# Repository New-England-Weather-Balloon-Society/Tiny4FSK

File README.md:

# Tiny4FSK - The Lightweight Horus Binary Tracker Built for HABs
**WORK IN PROGRESS** - Please do not rely on this as your only tracking system. Tiny4FSK is still in the R&D phase of development and testing.

**NEW** - Horus Binary v3! + quick lock mode and recovery mode

**STATE** - Main branch is stable!

## What is the Tiny4FSK project?
Tiny4FSK aims to be an ultra-tiny high-altitude tracking system. It runs on 1 AA battery that lasts for 10-17 hours (packet interval and power output can be adjusted to lengthen battery life). It runs on 4FSK (4-frequency shift keying), which means that it separates tones into 4 separate frequencies. Upon this, it uses the [Horus Binary v3](https://github.com/projecthorus/horusdemodlib) system, which is a relatively modern system popularly used with [RS41ng](https://github.com/mikaelnousiainen/RS41ng).

## What are High-Altitude Balloons?
High altitude balloons (HABs) allow space science enthusiasts to launch their own payloads to near-space (30km) at a cost of hundreds of dollars instead of millions of dollars.  This can be done for atmospheric research, breathtaking imagery, and scientific experimentation. While demanding meticulous planning, safety adherence, and technical skill in electronics and mechanics, this hobby rewards makers with a chance to get hands on with projects like electronic data loggers, camera systems, wireless communications, and more.
## Parts and Materials
This codebase is meant to work with the Tiny4FSK PCB, also available on this GitHub repository. Key components include:

 - **Microcontroller** - [SAMD21G18A](https://www.microchip.com/en-us/product/atsamd21g18). A modern Cortex-M0+ microcontroller by Microchip.
 - **TX Module** - [Si4063](https://www.silabs.com/wireless/proprietary/ezradiopro-sub-ghz-ics/device.si4063?tab=specs). A transceiver from Silicon Labs, similar to the Si4032 on RS41 radiosondes.
 - **GPS RX Module** - [ATGM336H](https://jlcpcb.com/partdetail/Zhongkewei-ATGM336H5N31/C90770). A cheap, high-performance GPS module from ZHONGKEWEI.
 - **Environmental Sensor** - [BME280](https://www.bosch-sensortec.com/products/environmental-sensors/humidity-sensors-bme280/). A proven sensor from Bosch for measuring temperature, pressure, and humidity.
 - **Boost Converter** - [TPS61200](https://www.ti.com/product/TPS61200). Boosts 1.5V battery level to 3.3V for the rest of the board from Texas Instruments.
 - **LDO Step-Down** - [MCP1700](https://www.microchip.com/en-us/product/mcp1700). A step-down converter from Microchip.

This list is not exhaustive. Additional components and passives are detailed in the schematic files.
## The Codebase
This code is modular and separated into several different files for easy expansion. These files are listed below:

 - **Tiny4FSK.ino** - Main Arduino file with control flow.
 - **config.h** - Configuration file for user parameters.
 - **crc_calc.cpp and crc_calc.h** - CRC16 generator files for parity bits.
 - **horus_l2.cpp and horus_l2.h** - Horus layer 2 file, Golay error correction algorithm.
 - **horus_binary_v3.cpp and horus_binary_v3.h** - Horus Binary v3 packet assembly and encoding functions.
 - **voltage.cpp and voltage.h** - Voltage detection using ADC values.
 - **si4063.cpp and si4063.h** - Si4063 driver files for radio transmission.
 - **4fsk_mod.cpp and 4fsk_mod.h** - 4FSK modulation functions.
 - **utils.cpp and utils.h** - A collection of utility functions.

# Step by Step Setup Guide
## Setting up the PCB

For pre-flight configuration, the USB board does not need to be broken off, and code can be uploaded normally by just plugging in the USB as it arrives. However, the breakout may be removed to save space during flights!

1. **Carefully** snap off the USB breakout board from the board.
2. Solder on the female 1x4 header row onto the underside of the USB breakout. Solder on the 1x4 male header row to the corresponding adjacent pins (labeled VSS, GND, D-, and D+).

3. To program the board, attach the USB breakout board as shown in the photo.  Once the board is programmed, the USB breakout board can be removed for flight.

## Antenna System
This system relies on the 70cm amateur radio band (420-450 MHz in the US), and requires an amateur radio license, issued by the FCC, to operate. A pre-cut braided copper *monopole* is included, optimized to transmit on this frequency. The included antenna is a quarter-wave monopole, meaning that the antenna is just a quarter of the wavelength of the signal, and yet it maintains a good SWR (quantification of how much signal is reflected back into the transmitter). There is a pad that supports a quarter-wave monopole, but also provides grounding pads for a coax connector if alternate antennas wish to be used.
<details>
<summary>Why does this work?</summary>
A 1/4 wave monopole antenna works by using a quarter of the wavelength of the signal, which creates a resonant frequency that efficiently radiates radio waves. The ground plane acts as a reflector, effectively doubling the antenna's length and improving signal strength and quality.
</details>
<br>

Solder the copper wire onto the center pin of the antenna connector (as depicted below).

## PCB Configuration
The Tiny4FSK PCB has many configurable operating modes, pins and power sources. This section will outline these parts of the PCB.

The PCB contains one jumper, JP1.

- **JP1** - Cut (desolder) to enable SW1 for power. During flight, the mechanical shock from the landing can cause the power switch to flip, so solder this jumper to disable this risk. (Bypasses SW1).

There are also two switches/buttons, SW1 and SW2.

- **SW1** - Battery power switch. Connects battery output to boost converter input. When the battery is connected, this functions as the main power switch.
- **SW2** - Reset button for the microcontroller.

There are two antenna pads, AE1 and AE2.
- **AE1** - L1 GPS band antenna
- **AE2** - 70cm antenna pad. For a guide to cut a proper antenna, refer to the above section.

Finally, the top left 3-row header allows for custom power options.
- **VBat** - A direct connection to the switching regulator input pin. This accepts between 1.3V and 6V.
- **GND** - Board ground.
- **3v3** - Regulated 3.3V node.

## Setting up the Code
Now that you've got all the hardware set up, time for programming!

## Setting up Arduino IDE
This project is based on the Arduino IDE workflow. Below steps outline steps necessary to install Arduino IDE and configure it for the SAMD microcontroller.

 1. Install [Arduino IDE](https://www.arduino.cc/en/software) from [here](https://www.arduino.cc/en/software).
 2. [Download the Arduino SAMD core](https://docs.arduino.cc/learn/starting-guide/cores/).
 3. Download necessary libraries from library manager:
    * Arduino Low Power (with dependencies)
    * TinyGPSPlus
    * Scheduler

**Optional** - The SAMD goes to sleep to save power. To achieve proper sleep, some edits to the SAMD core are necessary. To locate the wiring.c file on your computer, [follow this guide](https://support.arduino.cc/hc/en-us/articles/4415103213714-Find-sketches-libraries-board-cores-and-other-files-on-your-computer).

Windows: `C:/Users/[YOUR USER]/AppData/Local/Arduino15/packages/arduino/hardware/samd/1.8.14/cores/arduino`

Once there, comment out or completely delete the lines shown below:
```cpp
    // Defining VERY_LOW_POWER breaks Arduino APIs since all pins are considered INPUT at startup
    // However, it really lowers the power consumption by a factor of 20 in low power mode (0.03mA vs 0.6mA)
    #ifndef VERY_LOW_POWER
      // Setup all pins (digital and analog) in INPUT mode (default is nothing)
      for (uint32_t ul = 0 ; ul < NUM_DIGITAL_PINS ; ul++ )
      {
        pinMode( ul, INPUT ) ;
      }
    #endif
```
Arduino gives you an official warning: "This breaks Arduino APIs since all pins are considered INPUT at startup. However, it really lowers the power consumption by a factor of 20 in low power mode (0.03mA vs 0.6mA)". Testing has shown no adverse effects.

## Code Configuration
User configuration of this tracker is **required**. As this system uses amateur radio, you will need at least a Technician's level license (US). Configuration file is located in **config.h**. Open this file in Arduino IDE. Here are the parameters may need to be changed.

- `CALLSIGN` - Amateur radio callsign. This is required to stay legal!
- `CALLSIGN_WPM` - Speed to send the callsign, in morse code.
- `CALLSIGN_INTERVAL` - Interval to send the morse code callsign. Maximum interval in the US is 10 minutes.
- `FREQUENCY` - This is setting for your preferred TX frequency. The filter is optimized for 70cm radio band.
- `STATUS_LED` - Comment out to disable verbose status LEDs on PCB.
- `DEV_MODE` - Comment out for flight mode, uncomment during programming. Disables Serial and enables deep sleep modes for lower power consumption.
- `PACKET_INTERVAL` - Interval between 4FSK packets. The smaller the interval, the lower the battery life is.
- `OUTPUT_POWER` - 0-127. This is the output power of the radio module (suggested to keep at maximum).
- `FLAG_BAD_PACKET` - If the latest GPS values are bad, send out all zeroes (for time, position, speed, and altitude)(suggested).
- `QUICK_LOCK` - Quick lock mode lowers the output power and increases packet interval while the GPS doesn't have a lock. This helps with desensing the GPS receiver. Values return to previously-defined `PACKET_INTERVAL` and `OUTPUT_POWER` upon lock.
- `QUICK_LOCK_POWER` - Power level used while the GPS doesn't have a lock. Only applied if `QUICK_LOCK` mode is enabled.
- `QUICK_LOCK_INTERVAL` - Packet interval used while the GPS doesn't have a lock. Only applied if `QUICK_LOCK` mode is enabled.
- `RECOVERY_MODE` - If enabled, the tracker will send updates less frequently when on the ground to save power. Only occurs if the tracker detects it's in a flight.
- `RECOVER_MODE_INTERVAL` - Interval to transmit in recovery mode, when on the ground.
- `RECOVERY_MODE_FLIGHT_THRESHOLD` - Altitude threshold to consider ourselves in flight, in meters.
- `RECOVERY_MODE_LAND_THRESHOLD` - Altitude threshold to consider ourselves on the ground, in meters. Recovery mode will trigger below this altitude.

### Output power mapping

Approximate mapping from the `OUTPUT_POWER` numeric value to typical output in dBm:

| Value | Approx. dBm |
|------:|:-----------:|
| 127   | 19 dBm      |
| 100   | 18 dBm      |
| 80    | 16.5 dBm    |
| 60    | 14.5 dBm    |
| 40    | 11.4 dBm    |
| 20    | 5.6 dBm     |
| 0     | -45 dBm     |

<details>
<summary>How do I change these values?</summary>
If there is a pre-existing number or value next to the name of the setting name, you can replace that value with the desired value (e.g. replace the "N0CALL" with your callsign in double quotes, "W0MXX"). If there is no value next to the name, you need to comment out the setting to disable that functionality, or uncomment to enable that functionality (comments are defined by adding // at the start of the line).
</details>

<details>
<summary>A note on reprogramming without DEV_MODE, or: Why does the board continuously disconnect from the computer?</summary>
On the condition that DEV_MODE is uncommented, the microcontroller goes into deep sleep to conserve power. Part of this sleep cycle includes disabling the USB peripheral, causing the board to appear to continuously disconnect and reconnect. <em>This can easily be fixed by double-clicking the reset button. Doing so will enter the board into bootloader mode, which will attach the board onto a new USB port and disable any code. Once new code is uploaded, the board will appear on a different port on the computer.</em>
</details>

## Battery Life Expectations
Through a series of battery life tests on ground-level, we've created a graph approximating the battery life with reference to packet interval and transmit power.

These graphs only provide an approximation. Variation will still occur from battery to battery, and we always recommend testing yourself prior to flight and aiming for double the battery life necessary.

At maximum power (127):

All power levels from 0 (no amplifier) to 127 (max power):

All tests ran with quick lock off and 1x Energizer Ultimate Lithium AA.

## Upload the Code!
Once code configuration is complete, you may plug in a standard data USB-C cable into the breakout board, select the port in Arduino IDE, and select the upload button (marked by an arrow at the top). You should select the `Arduino Zero (Native USB Port)` as the board name.

## Testing
Once the code is uploaded, you'll see the green LED pulse briefly to indicate initialization. The behavior of that LED is outlined [here](#led-default-behavior). Now you'll need to set up a receive station on either a [laptop and an RTL-SDR](https://github.com/projecthorus/horusdemodlib/wiki/1.1-Horus-GUI-Reception-Guide-(Windows-Linux-OSX)), [Raspberry Pi and RTL-SDR](https://github.com/projecthorus/horusdemodlib/wiki/1.2--Raspberry-Pi-'Headless'-RX-Guide), or [any browser-enabled device with an RTL-SDR](https://horus.sondehub.org).

You should start decoding packets transmitted from the board with your configuration parameters. It may take up to 5 minutes to gain a GPS fix, depending on your location.

## LED Default Behavior

| Green LED Behavior | Meaning |
|--------------------|---------|
| Single 1s pulse    | GPS detected / Airborne mode set (single pulse during initialization) |
| Single 0.5s pulse  | Packet transmission (packet build / transmit — single short pulse) |
| Off                | Idle or deep sleep (no continuous blinking) |

## External Sensors
Tiny4FSK now offers compatibility with external sensors by automatically scanning I2C on startup. Some sensors come with the Tiny4FSK General Shield, which can be found on the [GitHub Repository](https://github.com/mpkendall/Tiny4FSK-Ecosystem). If you have any custom sensors which you would like me to add support for, please raise an [issue](https://github.com/New-England-Weather-Balloon-Society/Tiny4FSK/issues).

## PCBWay PCBs
The Revision 4 PCBs have been fabricated and assembled through PCBWay. Their high-quality fabrication and assembly services are truly commendable. I appreciated the ability to choose from many different component suppliers to select the exact components I needed. Additionally, their customer service is incredibly responsive and helpful, and quickly notified me of design issues. I highly recommend PCBWay for any of your PCB prototyping & assembly needs. Thank you, PCBWay, for graciously sponsoring this project!

## Contact Me!
To ask questions, kindly donate, or even say hi, feel free to contact me at this email: tiny4fsk@gmail.com. Thanks!

## Cited Works and Sources
- [RS41ng Project](https://github.com/mikaelnousiainen/RS41ng)
- [Horus Binary modulator and decoder repository](https://github.com/projecthorus/horusdemodlib)
- [SAMD21 product page](https://www.microchip.com/en-us/product/atsamd21g18)
- [Si4063 product page](https://www.silabs.com/wireless/proprietary/ezradiopro-sub-ghz-ics/device.si4063)
- [ATGM336H product page](https://www.u-blox.com/en/product/max-m10-series)
- [BME280 product page](https://www.bosch-sensortec.com/products/environmental-sensors/humidity-sensors-bme280)
- [TPS61200 product page](https://www.ti.com/product/TPS61200)
- [MCP1700 product page](https://www.microchip.com/en-us/product/mcp1700)

## Special Thanks
This project would not be possible without the following individuals:
 - Charlie Nicholson KC1SFR for collaboration.
 - Mark Jessop VK5QI for extensive support.
 - Mike Hojnowski KD2EAT for helping out with software and hardware issues.
 - Bob Phinney K5TEC for providing funding for this project.
 - Brett Miwa for schematic and PCB design help.
 - Joe KM1P for RF help.
 - My parents for motivation.

And these entities:
 - PCBWay for PCB prototyping and sponsorship!
 - Bagel Fund for sponsorship!
 - Hack Club for support and sponsorship!
 - New England Sci-Tech for providing a makerspace.
 - Sci-Tech Amateur Radio Society for expertise.
 - New England Weather Balloon Society for insights.
 - Digikey for part sourcing.

## License
Software and Documentation:
- [GNU GPL v3 license](https://choosealicense.com/licenses/gpl-3.0/)

Hardware License:
- [OSHW (US002611)](https://certification.oshwa.org/us002611.html) and [CERN Open Hardware Licence Version 2 - Weakly Reciprocal](https://choosealicense.com/licenses/cern-ohl-w-2.0/)

## Pictures

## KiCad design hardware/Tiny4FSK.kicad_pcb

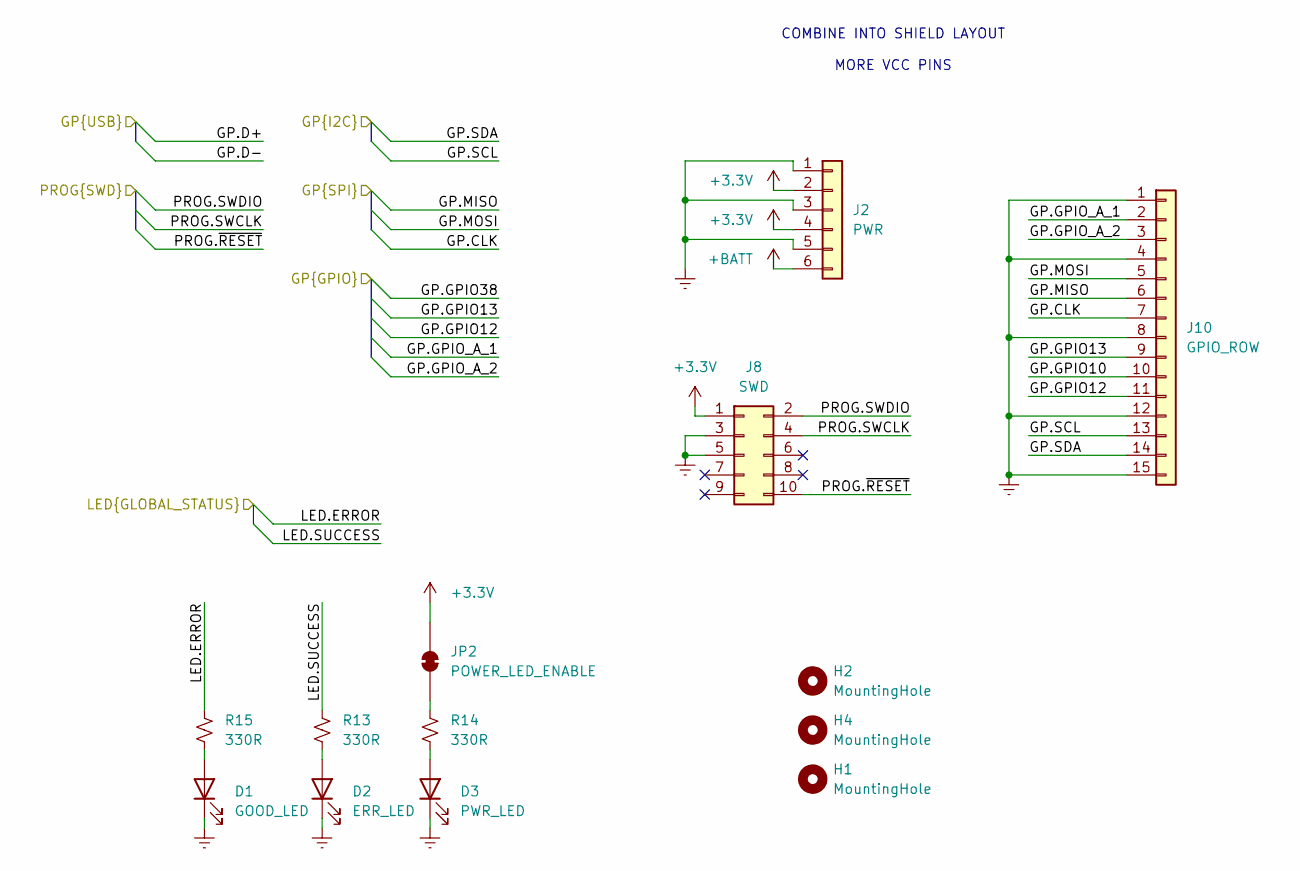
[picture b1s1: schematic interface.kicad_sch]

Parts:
D1: GOOD_LED; LED_0603_1608Metric; LCSC C2297
D2: ERR_LED; LED_0603_1608Metric; LCSC C84256
D3: PWR_LED; LED_0603_1608Metric; LCSC C84256
H1, H2, H4: MountingHole; MountingHole_2.2mm_M2
J2: PWR; PinHeader_1x06_P2.54mm_Vertical
J8: SWD; Pogo_2x05_P1.27mm
J10: GPIO_ROW; PinHeader_1x15_P2.54mm_Vertical
JP2: POWER_LED_ENABLE; SolderJumper-2_P1.3mm_Bridged_RoundedPad1.0x1.5mm
R13, R14, R15: 330R; C_0402_1005Metric; LCSC C23138

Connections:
+3.3V: J2.2, J2.4, J8.1, JP2.2 (B); also elsewhere on the board
+BATT: J2.6; also elsewhere on the board
/interface/GP.CLK: J10.7; also elsewhere on the board
/interface/GP.GPIO10: J10.10; also elsewhere on the board
/interface/GP.GPIO12: J10.11; also elsewhere on the board
/interface/GP.GPIO13: J10.9; also elsewhere on the board
/interface/GP.GPIO_A_1: J10.2; also elsewhere on the board
/interface/GP.GPIO_A_2: J10.3; also elsewhere on the board
/interface/GP.MISO: J10.6; also elsewhere on the board
/interface/GP.MOSI: J10.5; also elsewhere on the board
/interface/GP.SCL: J10.13; also elsewhere on the board
/interface/GP.SDA: J10.14; also elsewhere on the board
/interface/LED.ERROR: R15.1; also elsewhere on the board
/interface/LED.SUCCESS: R13.1; also elsewhere on the board
/interface/PROG.SWCLK: J8.4; also elsewhere on the board
/interface/PROG.SWDIO: J8.2; also elsewhere on the board
/interface/PROG.~RESET: J8.10; also elsewhere on the board
Earth: D1.1 (K), D2.1 (K), D3.1 (K), J2.1, J2.3, J2.5, J8.3, J8.5, J10.1, J10.4, J10.8, J10.12, J10.15; also elsewhere on the board
unnamed: D1.2 (A), R15.2
unnamed: D2.2 (A), R13.2
unnamed: D3.2 (A), R14.2
unnamed: JP2.1 (A), R14.1

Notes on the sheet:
COMBINE INTO SHIELD LAYOUT MORE VCC PINS

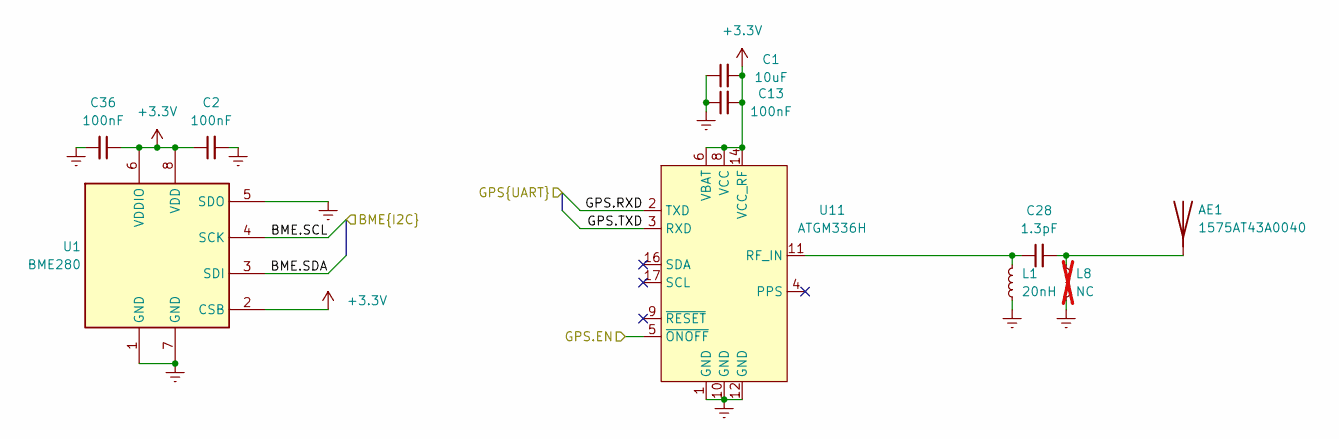
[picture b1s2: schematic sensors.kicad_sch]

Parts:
AE1: 1575AT43A0040; ANT_1575AT_JOT; LCSC C239243
C1: 10uF; C_0402_1005Metric; LCSC C19702
C2, C36: 100nF; C_0402_1005Metric; LCSC C52923
C13: 100nF; C_0402_1005Metric; LCSC C1525
C28: 1.3pF; C_0402_1005Metric; LCSC C1525
L1: 20nH; C_0402_1005Metric; LCSC C307609
L8: NC; L_0402_1005Metric; LCSC C307609; not fitted
U1: BME280; Bosch_LGA-8_2.5x2.5mm_P0.65mm_ClockwisePinNumbering; LCSC C92489
U11: ATGM336H; ublox_MAX

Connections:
+3.3V: C1.2, C2.1, C13.2, C36.1, U1.2 (CSB), U1.6 (VDDIO), U1.8 (VDD), U11.6 (VBAT), U11.8 (VCC), U11.14 (VCC_RF); also elsewhere on the board
/interface/GP.SCL: U1.4 (SCK); also elsewhere on the board
/interface/GP.SDA: U1.3 (SDI); also elsewhere on the board
/mcu/GPS.EN: U11.5 (~ONOFF); also elsewhere on the board
/mcu/RXD: U11.2 (TXD); also elsewhere on the board
/mcu/TXD: U11.3 (RXD); also elsewhere on the board
Earth: C1.1, C2.2, C13.1, C36.2, L1.1, L8.2, U1.1 (GND), U1.5 (SDO), U1.7 (GND), U11.1 (GND), U11.10 (GND), U11.12 (GND); also elsewhere on the board
unnamed: AE1.1 (A_1), C28.2, L8.1
unnamed: C28.1, L1.2, U11.11 (RF_IN)

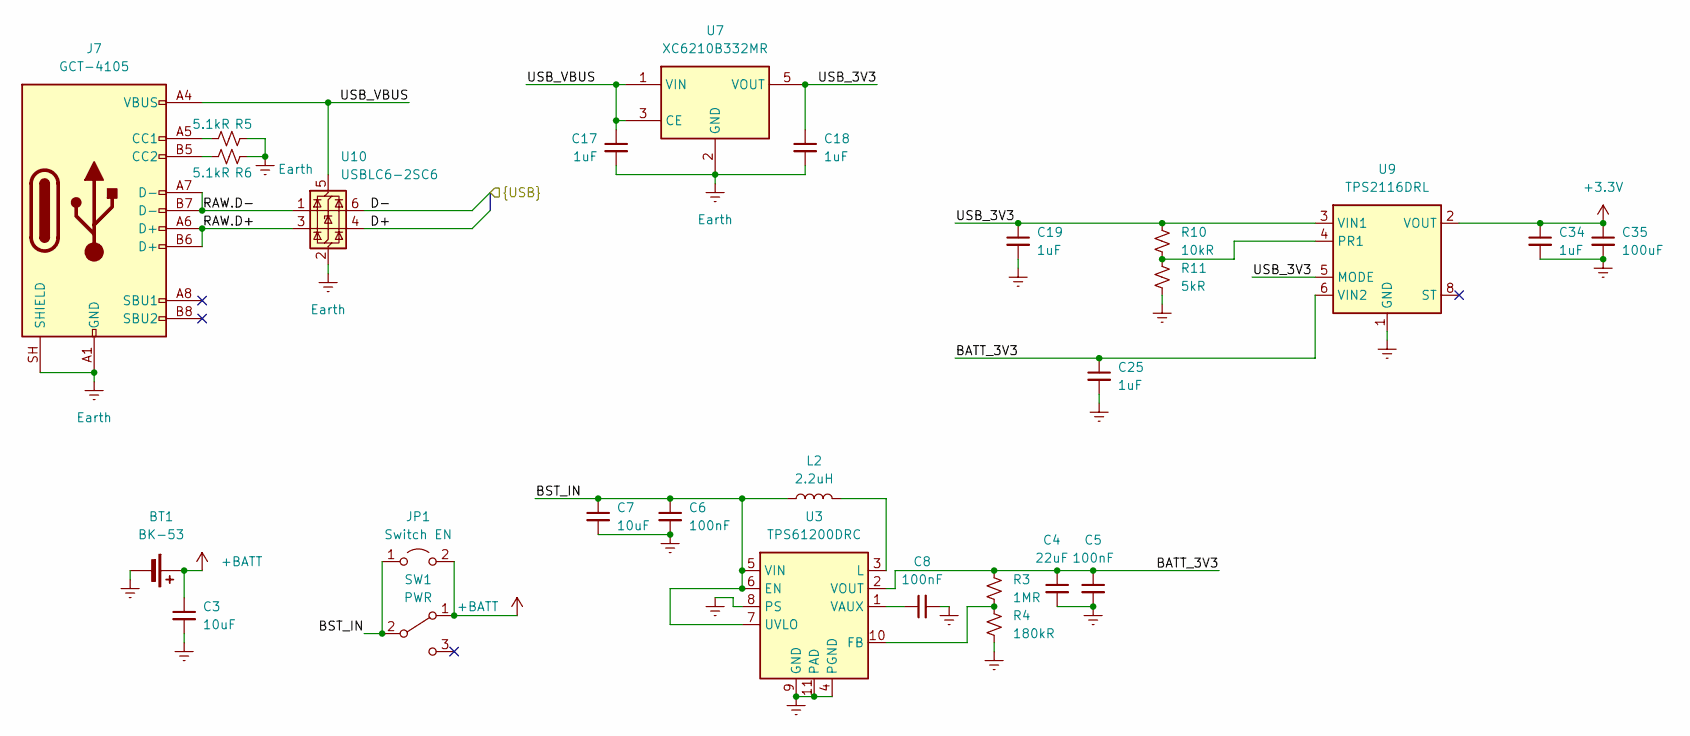
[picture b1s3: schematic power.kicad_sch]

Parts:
BT1: BK-53; BAT_BK-53
C3: 10uF; C_0402_1005Metric; LCSC C52923
C4: 22uF; C_0402_1005Metric; LCSC C59461
C5, C6, C8: 100nF; C_0402_1005Metric; LCSC C1525
C7: 10uF; C_0402_1005Metric; LCSC C19702
C17, C18, C19, C25, C34: 1uF; C_0402_1005Metric; LCSC C52923
C35: 100uF; C_0402_1005Metric; LCSC C52923
J7: GCT-4105; USB_C_Receptacle_GCT_USB4105-xx-A_16P_TopMnt_Horizontal; LCSC C2760486
JP1: Switch EN; SolderJumper-2_P1.3mm_Open_Pad1.0x1.5mm
L2: 2.2uH; L_Coilcraft_LPS3010; LCSC C2844756
R3: 1MR; R_0402_1005Metric; LCSC C26083
R4: 180kR; R_0402_1005Metric; LCSC C100276
R5, R6: 5.1kR; R_0402_1005Metric; LCSC C25905
R10: 10kR; R_0402_1005Metric
R11: 5kR; R_0402_1005Metric
SW1: PWR; SW_SPDT_PCM12; LCSC C963206
U3: TPS61200DRC; Texas_S-PVSON-N10_ThermalVias; LCSC C140320
U7: XC6210B332MR; SOT-23-5
U9: TPS2116DRL; SOT-583-8
U10: USBLC6-2SC6; SOT-23-6; LCSC C7519

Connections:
+3.3V: C34.1, C35.1, U9.2 (VOUT), U9.7 (VOUT); also elsewhere on the board
+BATT: BT1.1 (+), C3.1, JP1.2 (B), SW1.1 (A); also elsewhere on the board
/interface/GP.D+: U10.4 (I/O2); also elsewhere on the board
/interface/GP.D-: U10.6 (I/O1); also elsewhere on the board
/power/BATT_3V3: C4.1, C5.1, C25.1, R3.1, U3.2 (VOUT), U9.6 (VIN2)
/power/BST_IN: C6.1, C7.1, JP1.1 (A), L2.2, SW1.2 (B), U3.5 (VIN), U3.6 (EN), U3.7 (UVLO)
/power/RAW.D+: J7.A6 (D+), J7.B6 (D+), U10.3 (I/O2)
/power/RAW.D-: J7.A7 (D-), J7.B7 (D-), U10.1 (I/O1)
/power/USB_3V3: C18.1, C19.1, R10.2, U7.5 (VOUT), U9.3 (VIN1), U9.5 (MODE)
/power/USB_VBUS: C17.1, J7.A4 (VBUS), J7.A9 (VBUS), J7.B4 (VBUS), J7.B9 (VBUS), U7.1 (VIN), U7.3 (CE), U10.5 (VBUS)
Earth: BT1.2 (-), C3.2, C4.2, C5.2, C6.2, C7.2, C8.2, C17.2, C18.2, C19.2, C25.2, C34.2, C35.2, J7.A1 (GND), J7.A12 (GND), J7.B1 (GND), J7.B12 (GND), J7.SH (SHIELD), R4.2, R5.2, R6.2, R11.1, U3.4 (PGND), U3.8 (PS), U3.9 (GND), U3.11 (PAD), U7.2 (GND), U9.1 (GND), U10.2 (GND); also elsewhere on the board
unnamed: J7.A5 (CC1), R5.1
unnamed: J7.B5 (CC2), R6.1
unnamed: R3.2, R4.1, U3.10 (FB)
unnamed: L2.1, U3.3 (L)
unnamed: C8.1, U3.1 (VAUX)
unnamed: R10.1, R11.2, U9.4 (PR1)

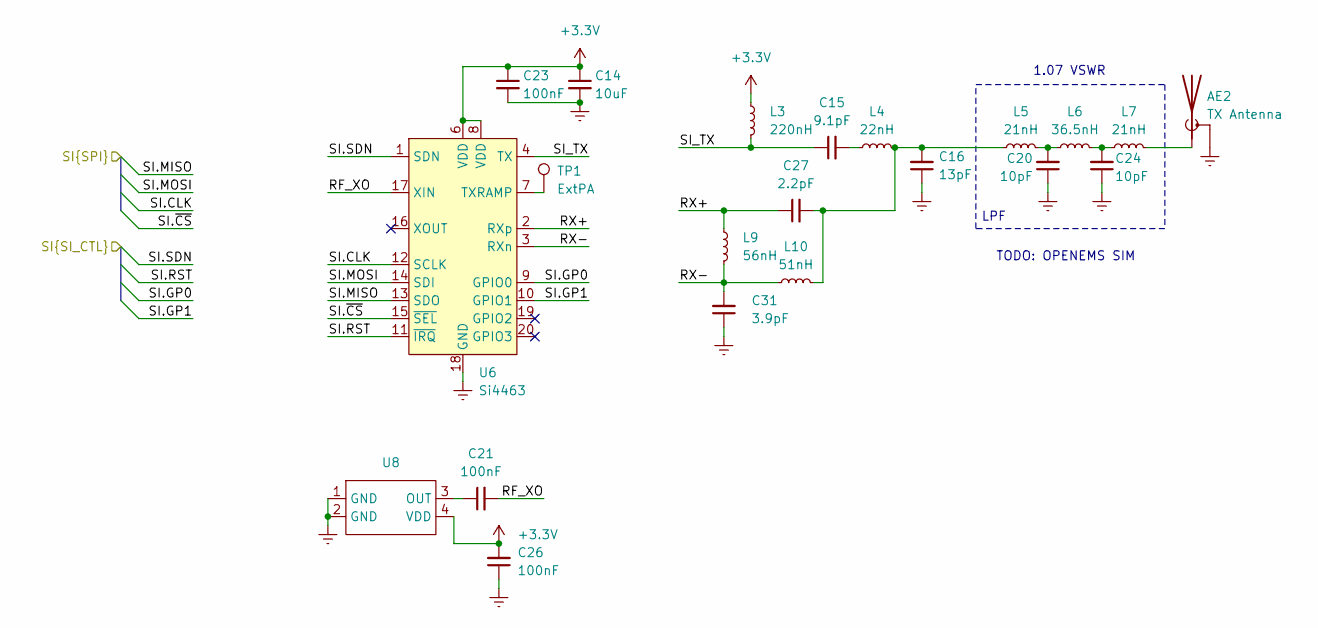
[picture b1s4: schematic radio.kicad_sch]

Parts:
AE2: TX Antenna; SMA_Samtec_SMA-J-P-H-ST-EM1_EdgeMount
C14: 10uF; C_0402_1005Metric; LCSC C19702
C15: 9.1pF; C_0402_1005Metric
C16: 13pF; C_0402_1005Metric
C20, C24: 10pF; C_0402_1005Metric
C21: 100nF; C_0402_1005Metric
C23, C26: 100nF; C_0402_1005Metric; LCSC C1525
C27: 2.2pF; C_0402_1005Metric
C31: 3.9pF; C_0402_1005Metric
L3: 220nH; L_0402_1005Metric
L4: 22nH; L_0402_1005Metric
L5, L7: 21nH; L_0402_1005Metric
L6: 36.5nH; L_0402_1005Metric
L9: 56nH; L_0402_1005Metric
L10: 51nH; L_0402_1005Metric
TP1: ExtPA; TestPoint_Pad_D1.0mm
U6: Si4463; QFN-20-1EP_4x4mm_P0.5mm_EP2.6x2.6mm_ThermalVias
U8: Crystal_SMD_2016-4Pin_2.0x1.6mm; LCSC C135223

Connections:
+3.3V: C14.1, C23.1, C26.2, L3.1, U6.6 (VDD), U6.8 (VDD), U8.4 (VDD); also elsewhere on the board
/interface/GP.CLK: U6.12 (SCLK); also elsewhere on the board
/interface/GP.MISO: U6.13 (SDO); also elsewhere on the board
/interface/GP.MOSI: U6.14 (SDI); also elsewhere on the board
/interface/GP.~CS: U6.15 (~SEL); also elsewhere on the board
/mcu/SI.GP0: U6.9 (GPIO0); also elsewhere on the board
/mcu/SI.GP1: U6.10 (GPIO1); also elsewhere on the board
/mcu/SI.RST: U6.11 (~IRQ); also elsewhere on the board
/mcu/SI.SDN: U6.1 (SDN); also elsewhere on the board
/radio/RF_XO: C21.2, U6.17 (XIN)
/radio/RX+: C27.1, L9.1, U6.2 (RXp)
/radio/RX-: C31.2, L9.2, L10.1, U6.3 (RXn)
/radio/SI_TX: C15.1, L3.2, U6.4 (TX)
Earth: AE2.2 (Shield), C14.2, C16.1, C20.1, C23.2, C24.1, C26.1, C31.1, U6.18 (GND), U6.21 (GND), U8.1 (GND), U8.2 (GND); also elsewhere on the board
unnamed: AE2.1 (RF), L7.2
unnamed: C15.2, L4.1
unnamed: C16.2, C27.2, L4.2, L5.1, L10.2
unnamed: C20.2, L5.2, L6.1
unnamed: C24.2, L6.2, L7.1
unnamed: TP1.1 (1_1), U6.7 (TXRAMP)
unnamed: C21.1, U8.3 (OUT)

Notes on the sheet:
1.07 VSWR
TODO: OPENEMS SIM
LPF

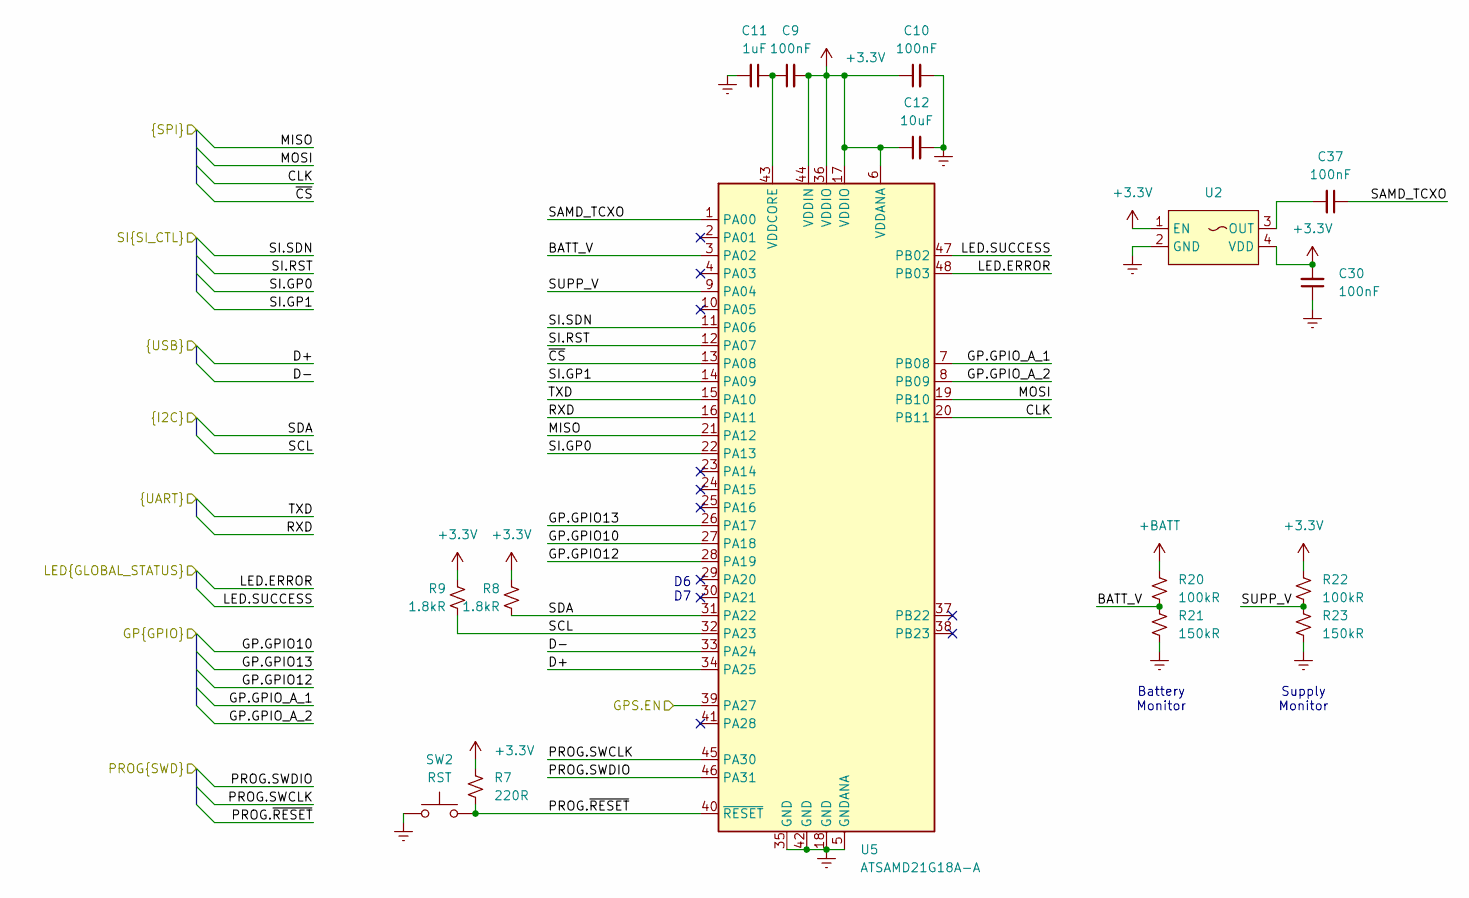
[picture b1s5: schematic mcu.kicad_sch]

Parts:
C9, C10, C30, C37: 100nF; C_0402_1005Metric; LCSC C1525
C11: 1uF; C_0402_1005Metric; LCSC C52923
C12: 10uF; C_0402_1005Metric; LCSC C19702
R7: 220R; R_0402_1005Metric; LCSC C25091
R8, R9: 1.8kR; R_0402_1005Metric; LCSC C4177
R20, R22: 100kR; C_0402_1005Metric; LCSC C26083
R21, R23: 150kR; C_0402_1005Metric; LCSC C26083
SW2: RST; SW_SPST_TS-1088-xR020; LCSC C2888954
U2: Crystal_SMD_2016-4Pin_2.0x1.6mm
U5: ATSAMD21G18A-A; TQFP-48_7x7mm_P0.5mm; LCSC C78624

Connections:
+3.3V: C9.2, C10.1, C12.1, C30.2, R7.2, R8.1, R9.1, R22.1, U2.1 (EN), U2.4 (VDD), U5.6 (VDDANA), U5.17 (VDDIO), U5.36 (VDDIO), U5.44 (VDDIN); also elsewhere on the board
+BATT: R20.1; also elsewhere on the board
/interface/GP.CLK: U5.20 (PB11); also elsewhere on the board
/interface/GP.D+: U5.34 (PA25); also elsewhere on the board
/interface/GP.D-: U5.33 (PA24); also elsewhere on the board
/interface/GP.GPIO10: U5.27 (PA18); also elsewhere on the board
/interface/GP.GPIO12: U5.28 (PA19); also elsewhere on the board
/interface/GP.GPIO13: U5.26 (PA17); also elsewhere on the board
/interface/GP.GPIO_A_1: U5.7 (PB08); also elsewhere on the board
/interface/GP.GPIO_A_2: U5.8 (PB09); also elsewhere on the board
/interface/GP.MISO: U5.21 (PA12); also elsewhere on the board
/interface/GP.MOSI: U5.19 (PB10); also elsewhere on the board
/interface/GP.SCL: R9.2, U5.32 (PA23); also elsewhere on the board
/interface/GP.SDA: R8.2, U5.31 (PA22); also elsewhere on the board
/interface/GP.~CS: U5.13 (PA08); also elsewhere on the board
/interface/LED.ERROR: U5.48 (PB03); also elsewhere on the board
/interface/LED.SUCCESS: U5.47 (PB02); also elsewhere on the board
/interface/PROG.SWCLK: U5.45 (PA30); also elsewhere on the board
/interface/PROG.SWDIO: U5.46 (PA31); also elsewhere on the board
/interface/PROG.~RESET: R7.1, SW2.2, U5.40 (~RESET); also elsewhere on the board
/mcu/BATT_V: R20.2, R21.1, U5.3 (PA02)
/mcu/GPS.EN: U5.39 (PA27); also elsewhere on the board
/mcu/RXD: U5.16 (PA11); also elsewhere on the board
/mcu/SAMD_TCXO: C37.1, U5.1 (PA00)
/mcu/SI.GP0: U5.22 (PA13); also elsewhere on the board
/mcu/SI.GP1: U5.14 (PA09); also elsewhere on the board
/mcu/SI.RST: U5.12 (PA07); also elsewhere on the board
/mcu/SI.SDN: U5.11 (PA06); also elsewhere on the board
/mcu/SUPP_V: R22.2, R23.1, U5.9 (PA04)
/mcu/TXD: U5.15 (PA10); also elsewhere on the board
Earth: C10.2, C11.2, C12.2, C30.1, R21.2, R23.2, SW2.1, U2.2 (GND), U5.5 (GNDANA), U5.18 (GND), U5.35 (GND), U5.42 (GND); also elsewhere on the board
unnamed: C37.2, U2.3 (OUT)
unnamed: C9.1, C11.1, U5.43 (VDDCORE)

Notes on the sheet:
Battery Monitor
Supply Monitor
D6 D7

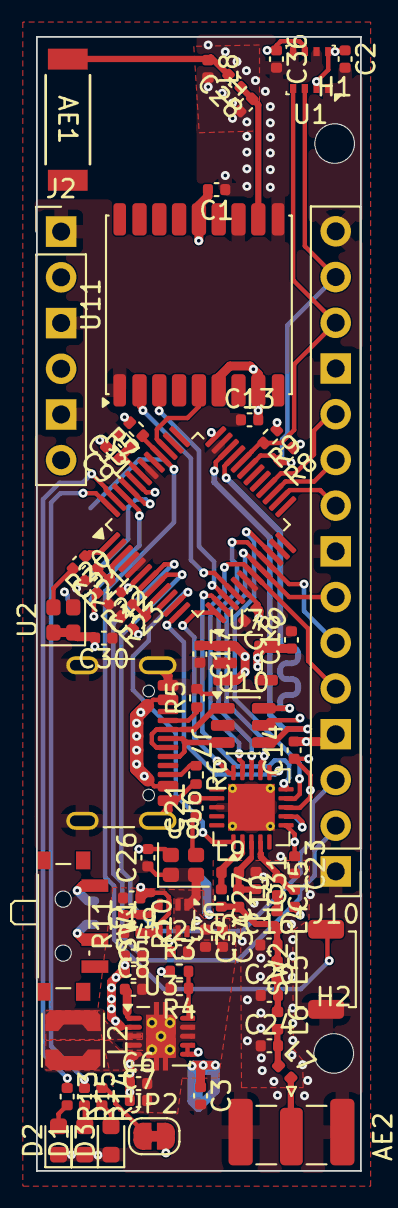
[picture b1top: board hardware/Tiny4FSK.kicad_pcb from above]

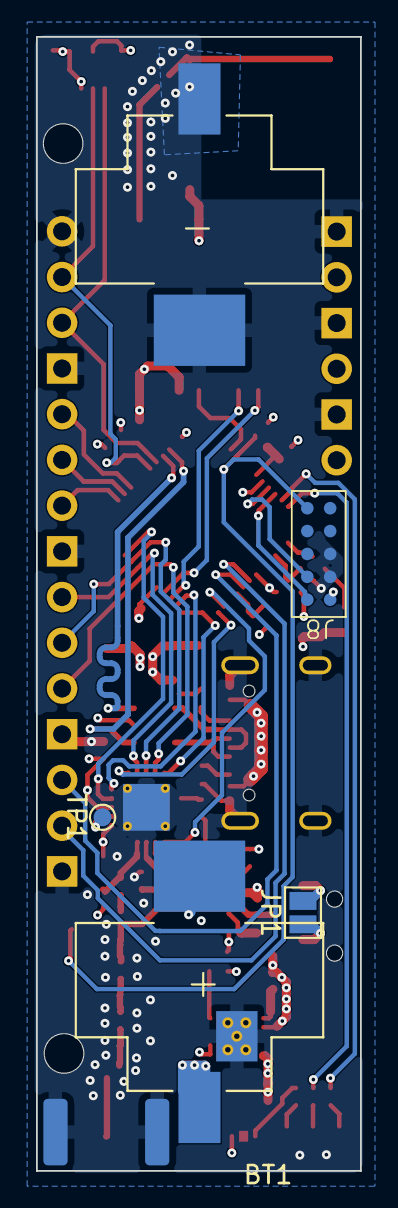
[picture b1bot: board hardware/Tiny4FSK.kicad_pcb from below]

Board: 4 copper layers, 18.0 x 63.0 mm, 87 parts (4 on the bottom side), 62 nets.

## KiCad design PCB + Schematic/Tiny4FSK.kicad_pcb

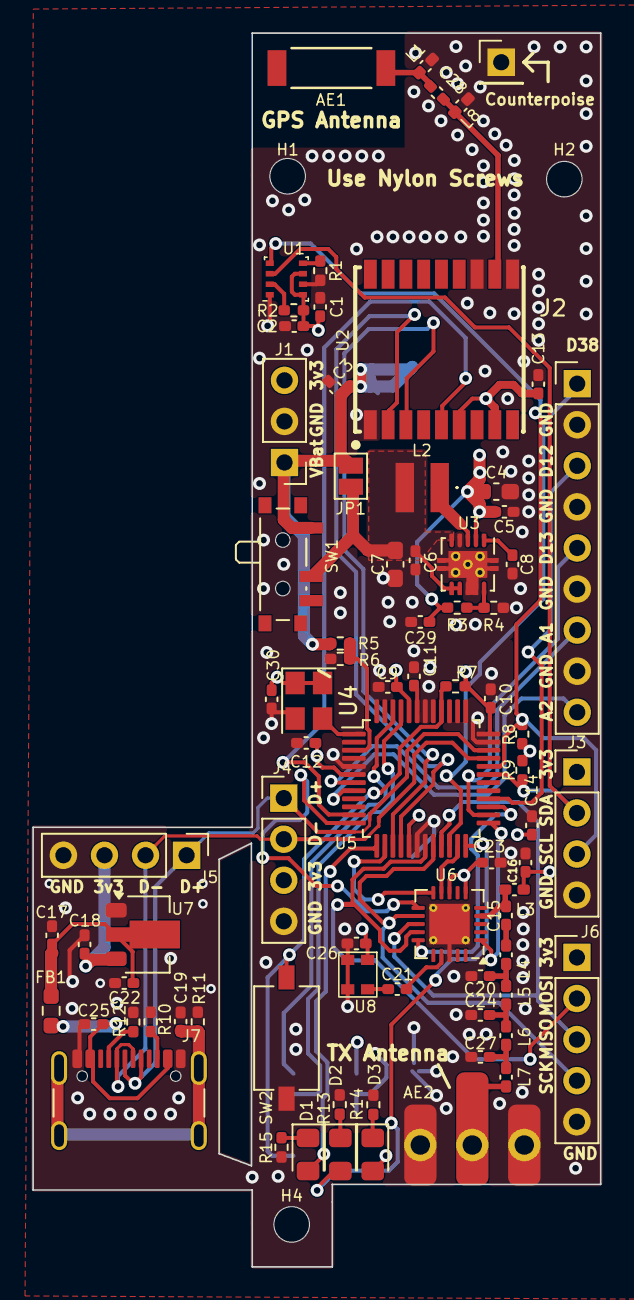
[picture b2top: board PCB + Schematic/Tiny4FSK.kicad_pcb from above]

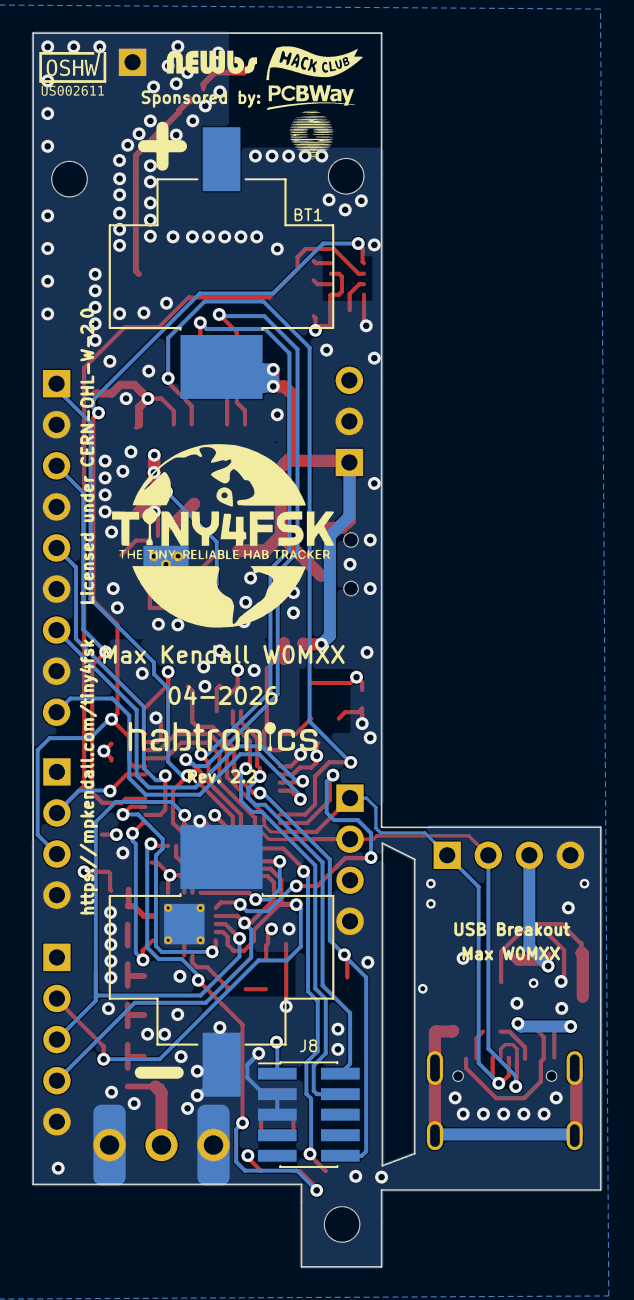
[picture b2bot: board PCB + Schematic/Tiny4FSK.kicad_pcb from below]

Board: 4 copper layers, 35.1 x 76.3 mm, 83 parts (2 on the bottom side), 55 nets.

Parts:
AE1: 1575AT43A0040; ANT_1575AT_JOT
AE2: TX Antenna; Antenna_Whip
BT1: BK-53; BAT_53
C1, C14: 10uF; C_0402_1005Metric_Pad0.74x0.62mm_HandSolder
C2, C3, C11, C18, C22: 1uF; C_0402_1005Metric_Pad0.74x0.62mm_HandSolder
C4: 22uF; C_0603_1608Metric_Pad1.08x0.95mm_HandSolder
C5, C8, C9, C13, C16, C23, C29: 100nF; C_0402_1005Metric_Pad0.74x0.62mm_HandSolder
C6, C10, C17, C25, C26, C30: 100 nF; C_0402_1005Metric_Pad0.74x0.62mm_HandSolder
C7: 10 uF; C_0603_1608Metric_Pad1.08x0.95mm_HandSolder
C12: 10 uF; C_0402_1005Metric_Pad0.74x0.62mm_HandSolder
C15: 9.1 pF; C_0402_1005Metric_Pad0.74x0.62mm_HandSolder
C19: 4.7 nF; C_0402_1005Metric_Pad0.74x0.62mm_HandSolder
C20: 8 pF; C_0402_1005Metric_Pad0.74x0.62mm_HandSolder
C21: 100 pF; C_0402_1005Metric_Pad0.74x0.62mm_HandSolder
C24: 6 pF; C_0402_1005Metric_Pad0.74x0.62mm_HandSolder
C27: 5 pF; C_0402_1005Metric_Pad0.74x0.62mm_HandSolder
C28: 2.7pF; C_0402_1005Metric_Pad0.74x0.62mm_HandSolder
D1: Success; LED_0805_2012Metric_Pad1.15x1.40mm_HandSolder
D2: Error; LED_0805_2012Metric_Pad1.15x1.40mm_HandSolder
D3: Power; LED_0805_2012Metric_Pad1.15x1.40mm_HandSolder
FB1: BLM18AG121SN1D; R_0603_1608Metric_Pad0.98x0.95mm_HandSolder
H1, H2, H4: MountingHole; MountingHole_2.2mm_M2
J1: Power Ext; PinHeader_1x03_P2.54mm_Vertical
J2: GPIO; PinHeader_1x09_P2.54mm_Vertical
J3: I2C; PinHeader_1x04_P2.54mm_Vertical
J4: USB; PinHeader_1x04_P2.54mm_Vertical
J5: USB Breakout; PinHeader_1x04_P2.54mm_Vertical
J6: SPI; PinHeader_1x05_P2.54mm_Vertical
J7: USBC; USB_C_Receptacle_GCT_USB4105-xx-A_16P_TopMnt_Horizontal
J8: SWD; PinHeader_2x05_P1.27mm_Vertical_SMD
J9: Counterpoise; PinHeader_1x01_P2.54mm_Vertical
JP1: Switch EN; SolderJumper-2_P1.3mm_Open_Pad1.0x1.5mm
L1, L8: 3.9 nH; L_0402_1005Metric_Pad0.77x0.64mm_HandSolder
L2: 2.2uH; LPS3015222MRB
L3: 220 nH; L_0402_1005Metric_Pad0.77x0.64mm_HandSolder
L4, L5, L6, L7: 14 nH; L_0402_1005Metric_Pad0.77x0.64mm_HandSolder
R1, R2: 10k; R_0402_1005Metric_Pad0.72x0.64mm_HandSolder
R3, R5, R6, R11: 1M; R_0402_1005Metric_Pad0.72x0.64mm_HandSolder
R4: 180k; R_0402_1005Metric_Pad0.72x0.64mm_HandSolder
R7: 220; R_0402_1005Metric_Pad0.72x0.64mm_HandSolder
R8, R9: 1.8k; R_0402_1005Metric_Pad0.72x0.64mm_HandSolder
R10, R12: 5k1; R_0402_1005Metric_Pad0.72x0.64mm_HandSolder
R13, R14, R15: 330; R_0402_1005Metric_Pad0.72x0.64mm_HandSolder
SW1: Power Switch; SW_SPDT_PCM12
SW2: RST; SW_Tactile_SPST_NO_Straight_CK_PTS636Sx25SMTRLFS
U1: BME280; Bosch_LGA-8_2.5x2.5mm_P0.65mm_ClockwisePinNumbering
U2: ATGM336H
U3: TPS61200DRC; Texas_S-PVSON-N10_ThermalVias
U4: ECS-327TXO-2012; Crystal_SMD_3225-4Pin_3.2x2.5mm
U5: ATSAMD21G18A-A; TQFP-48_7x7mm_P0.5mm
U6: SI4063; QFN-20-1EP_4x4mm_P0.5mm_EP2.5x2.5mm_ThermalVias
U7: Linear Step-Down; MCP1700
U8: ECS-TXO-20CSMV4

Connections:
+3.3V: C1.2, C2.1, C4.1, C5.1, C9.2, C10.1, C12.1, C13.2, C14.1, C16.2, C18.1, C23.1, C26.2, C29.1, C30.2, D3.2 (A), J1.3, J3.1, J4.3, J5.3, J6.1, J8.1, L3.1, R2.1, R3.1, R7.2, R8.1, R9.2, U1.6 (VDDIO), U1.8 (VDD), U2.6 (VBAT), U2.8 (VCC), U3.2 (VOUT), U4.1 (EN), U4.4 (VDD), U5.6 (VDDANA), U5.17 (VDDIO), U5.36 (VDDIO), U5.44 (VDDIN), U6.6 (VDD_1), U6.8 (VDD_2), U7.2 (VO), U8.4 (VDD)
+BATT: BT1.1 (+), C3.1, J1.1, JP1.2 (B), R5.1, SW1.1 (A)
A1: J2.7, U5.7 (PB08)
A2: J2.9, U5.8 (PB09)
ANT_GPS: C28.1, L8.2, U2.11 (RF_IN)
BATT_SENSE: R5.2, R6.1, U5.3 (PA02)
BST_IN: C6.1, C7.1, JP1.1 (A), L2.2, SW1.2 (B), U3.5 (VIN), U3.6 (EN), U3.7 (UVLO)
D12: J2.3, U5.28 (PA19)
D13: J2.5, U5.26 (PA17)
D38: J2.1, U5.22 (PA13)
D+: J4.1, J5.1, J7.A6 (D+), J7.B6 (D+), U5.34 (PA25)
D-: J4.2, J5.2, J7.A7 (D-), J7.B7 (D-), U5.33 (PA24)
ERROR: D2.2 (A), U5.24 (PA15)
Earth: AE2.2 (Shield), BT1.2 (-), C1.1, C2.2, C3.2, C4.2, C5.2, C6.2, C7.2, C8.2, C9.1, C10.2, C11.2, C12.2, C13.1, C14.2, C16.1, C17.2, C18.2, C19.1, C20.2, C22.1, C23.2, C24.2, C25.2, C26.1, C27.2, C29.2, C30.1, J1.2, J2.2, J2.4, J2.6, J2.8, J3.4, J4.4, J5.4, J6.5, J7.A1 (GND), J7.A12 (GND), J7.B1 (GND), J7.B12 (GND), J8.3, J8.5, J9.1 (Pin_1_1), L1.1, L8.1, R1.2, R4.2, R6.2, R10.1, R11.2, R12.1, R13.2, R14.2, R15.2, SW2.1, U1.1 (GND), U1.7 (GND), U2.1 (GND), U2.10 (GND), U2.12 (GND), U3.4 (PGND), U3.8 (PS), U3.9 (GND), U3.11 (PAD), U4.2 (GND), U5.5 (GNDANA), U5.18 (GND), U5.35 (GND), U5.42 (GND), U6.18 (GND_1), U6.21 (GND_2), U7.1 (GND), U8.1 (GND), U8.2 (GND)
GPIO0: U5.23 (PA14), U6.9 (GPIO0)
GPIO1: U5.14 (PA09), U6.10 (GPIO1)
GPS_EN: U2.5 (ONOFF), U5.11 (PA06)
LIN: C17.1, C22.2, FB1.2, U7.3 (VI)
MISO: J6.3, U5.21 (PA12), U6.13 (SDO)
MOSI: J6.2, U5.19 (PB10), U6.14 (SDI)
unnamed: AE1.1 (A_1), C28.2, L1.2
unnamed: AE2.1 (RF), L7.2
unnamed: C15.2, L4.1
unnamed: C20.1, L4.2, L5.1
unnamed: C24.1, L5.2, L6.1
unnamed: C27.1, L6.2, L7.1
unnamed: D1.1 (K), R15.1
unnamed: D2.1 (K), R13.1
unnamed: D3.1 (K), R14.1
unnamed: J7.A5 (CC1), R12.2
unnamed: J7.B5 (CC2), R10.2
unnamed: C19.2, J7.S1 (SHIELD), R11.1
unnamed: R2.2, U1.2 (CSB)
unnamed: R1.1, U1.5 (SDO)
unnamed: R3.2, R4.1, U3.10 (FB)
unnamed: L2.1, U3.3 (L)
unnamed: C8.1, U3.1 (VAUX)
unnamed: C11.1, U5.43 (VDDCORE)
unnamed: C21.2, U6.17 (XIN)
RF_ANT: C15.1, L3.2, U6.4 (TX)
RF_RST: U5.12 (PA07), U6.11 (NIRQ)
RF_SS: U5.27 (PA18), U6.15 (NSEL)
RF_XO: C21.1, U8.3 (CLK_OUT)
RXD: U2.2 (TXD), U5.16 (PA11)
SCK: J6.4, U5.20 (PB11), U6.12 (SCLK)
SCL: J3.3, R8.2, U1.4 (SCK), U5.32 (PA23)
SDA: J3.2, R9.1, U1.3 (SDI), U5.31 (PA22)
SDN: U5.25 (PA16), U6.1 (SDN)
SUCCESS: D1.2 (A), U5.13 (PA08)
SWCLK: J8.4, U5.45 (PA30)
SWDIO: J8.2, U5.46 (PA31)
TCXO: U4.3 (OUTPUT), U5.1 (PA00)
TXD: U2.3 (RXD), U5.15 (PA10)
USB: C25.1, FB1.1, J7.A4 (VBUS), J7.A9 (VBUS), J7.B4 (VBUS), J7.B9 (VBUS)
nRST: J8.10, R7.1, SW2.2, U5.40 (~RESET)

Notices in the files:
PCB + Schematic/Tiny4FSK.kicad_pcb:
Licensed under CERN-OHL-W-2.0
